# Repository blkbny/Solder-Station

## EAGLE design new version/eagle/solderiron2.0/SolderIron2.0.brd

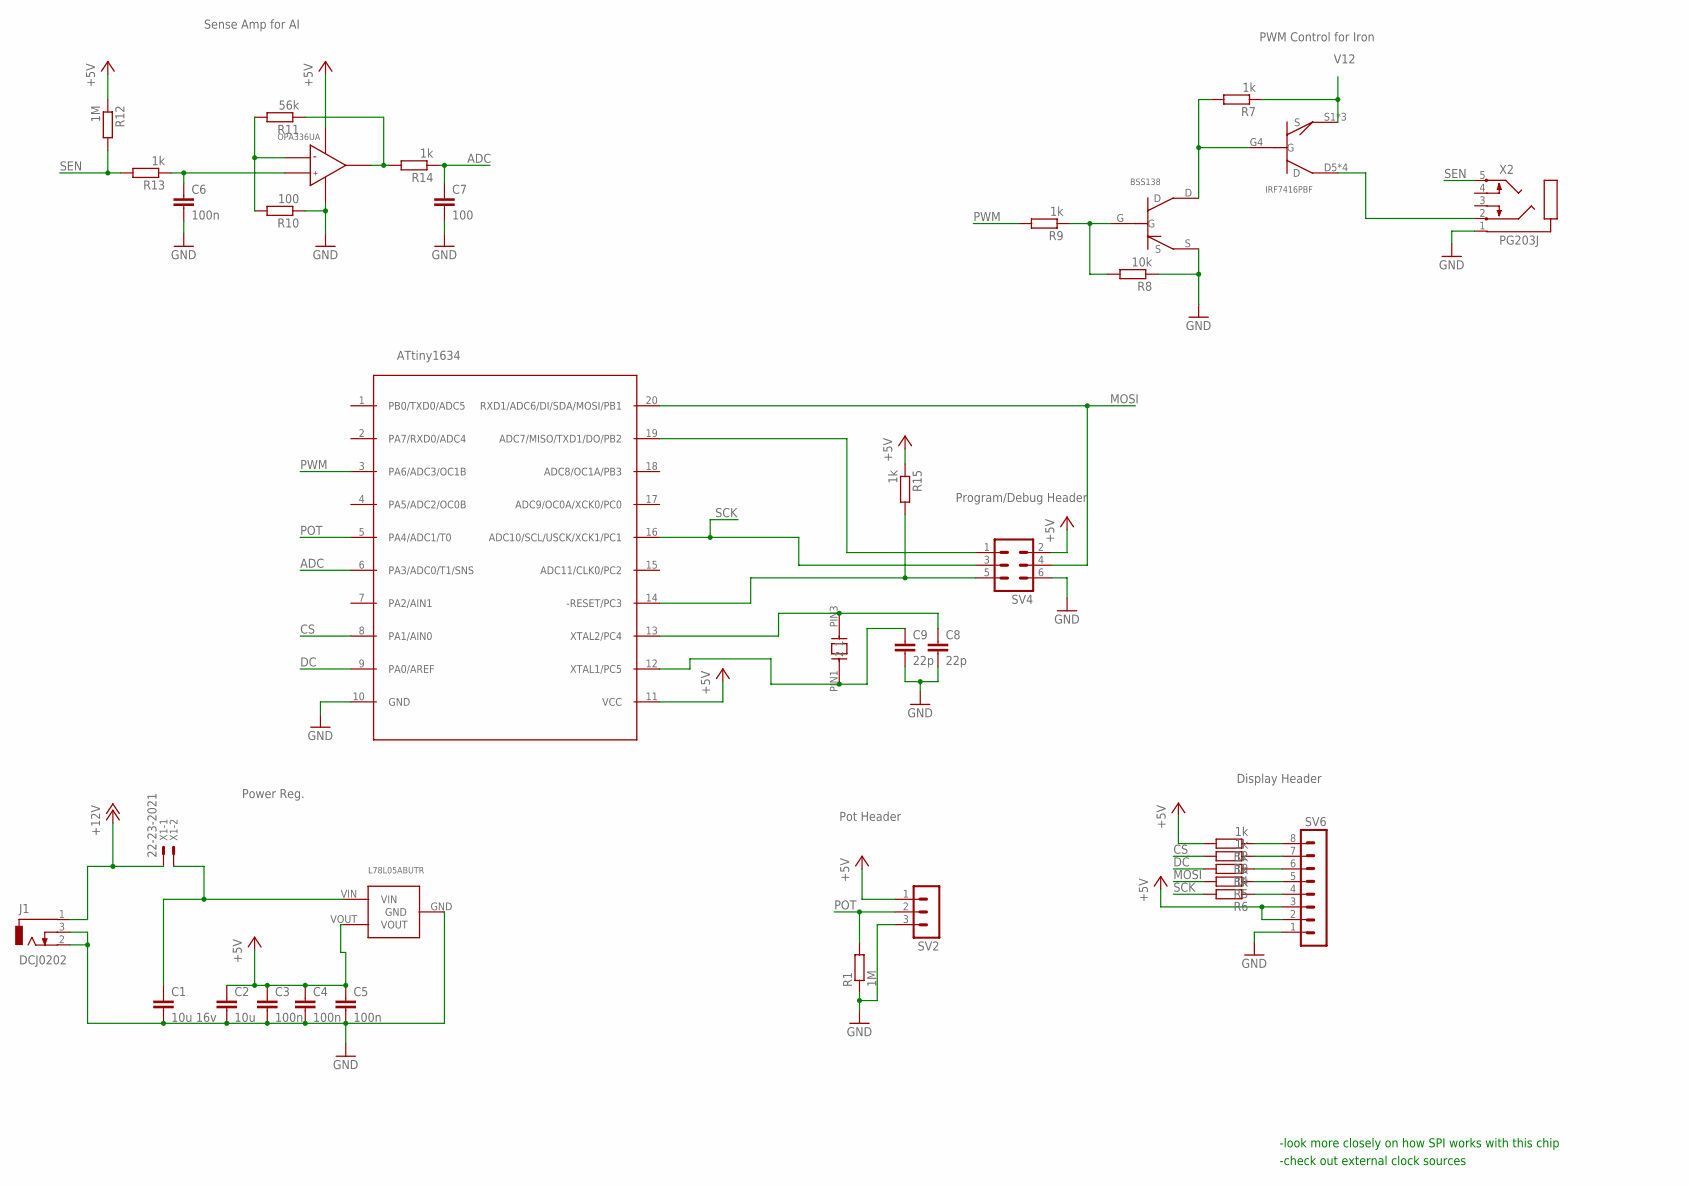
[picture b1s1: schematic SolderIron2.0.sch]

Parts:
C1: 10u 16v; C1206
C2: 10u; C1206
C3, C4, C5, C6: 100n; C1206
C7: 100; C1206
C8, C9: 22p; C1206
J1: DCJ0202; POWERJACK2.1MM
R1, R12: 1M; R0603
R2, R3, R4, R5, R6, R7, R9, R13, R14, R15: 1k; R0603
R8: 10k; R0603
R10: 100; R0603
R11: 56k; R0603
SV2: MA03-1
SV4: MA03-2
SV6: MA08-1
U$1: IRF7416PBF; 8-SOIC
U$2: L78L05ABUTR; SOT89-3
U$3: BSS138; SOT-23
U$4: OPA336UA; 8-SOIC
U$5: ATTINY1634; SOIC20
U$6: CX3225GB12000H0KPSC1; 4-SIZ
X1: 22-23-2021
X2: PG203J

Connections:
+5V: C2.1, C3.1, C4.1, C5.1, R2.2, R12.1, R15.1, SV2.1, SV4.2, SV6.2, SV6.3, U$2.VOUT, U$4.D7 (V+), U$5.11 (VCC)
+12V: J1.1, X1.1
ADC: C7.1, R14.1, U$5.6 (PA3/ADC0/T1/SNS)
CS: R3.2, U$5.8 (PA1/AIN0)
DC: R4.2, U$5.9 (PA0/AREF)
GND: C1.2, C2.2, C3.2, C4.2, C5.2, C6.2, C7.2, C8.2, C9.2, J1.2 (3), J1.3 (2), R1.1, R8.1, R10.1, SV2.3, SV4.6, SV6.1, U$2.GND, U$3.S, U$4.G4 (V-), U$5.10 (GND), X2.1
MOSI: R5.2, SV4.4, U$5.20 (RXD1/ADC6/DI/SDA/MOSI/PB1)
unnamed: C8.1, U$5.13 (XTAL2/PC4), U$6.PIN3 (2)
unnamed: R2.1, SV6.8
unnamed: R3.1, SV6.7
unnamed: R4.1, SV6.6
unnamed: R5.1, SV6.5
unnamed: R6.1, SV6.4
unnamed: U$1.D5 (D), U$1.D6 (D), U$1.D7 (D), U$1.D8 (D), X2.2
unnamed: R7.2, U$1.G4 (G), U$3.D
unnamed: R8.2, R9.1, U$3.G
unnamed: R10.2, R11.2, U$4.S2 (IN-)
unnamed: R11.1, R14.2, U$4.D6 (OUTPUT)
unnamed: C6.1, R13.1, U$4.S3 (IN+)
unnamed: C9.1, U$5.12 (XTAL1/PC5), U$6.PIN1 (1)
unnamed: SV4.1, U$5.19 (ADC7/MISO/TXD1/DO/PB2)
unnamed: R15.2, SV4.5, U$5.14 (-RESET/PC3)
POT: R1.2, SV2.2, U$5.5 (PA4/ADC1/T0)
PWM: R9.2, U$5.3 (PA6/ADC3/OC1B)
SCK: R6.2, SV4.3, U$5.16 (ADC10/SCL/USCK/XCK1/PC1)
SEN: R12.2, R13.2, X2.5
V12: C1.1, R7.1, U$1.S1 (S), U$1.S2 (S), U$1.S3 (S), U$2.VIN, X1.2

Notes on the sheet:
Power Reg.
Pot Header
Display Header
PWM Control for Iron
Sense Amp for AI
Program/Debug Header
-look more closely on how SPI works with this chip
-check out external clock sources

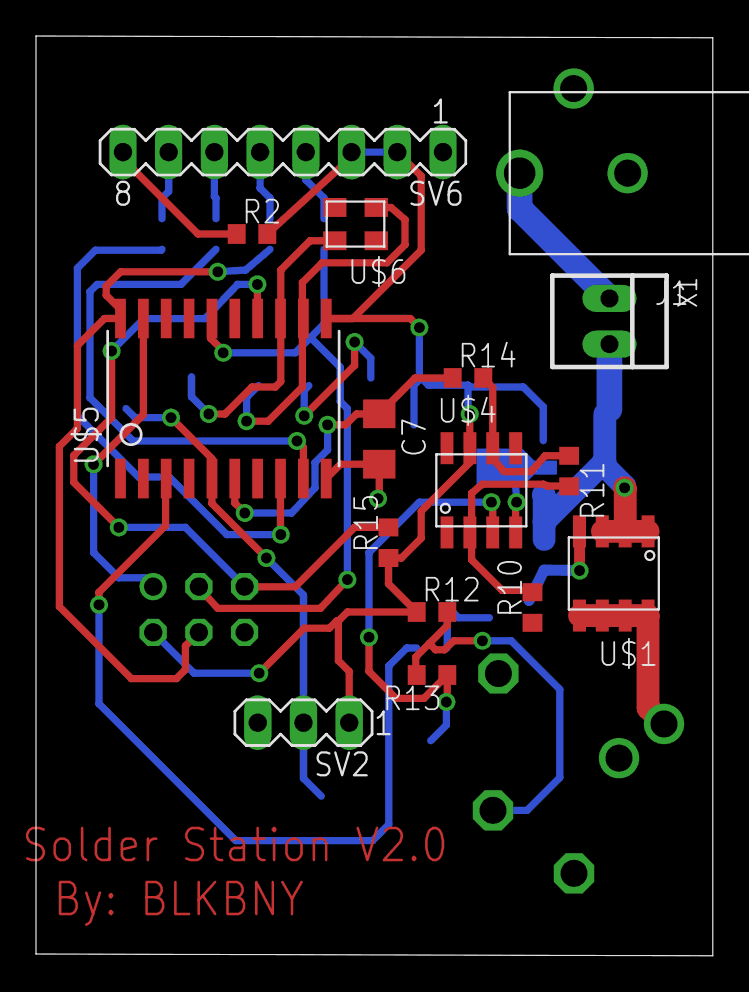
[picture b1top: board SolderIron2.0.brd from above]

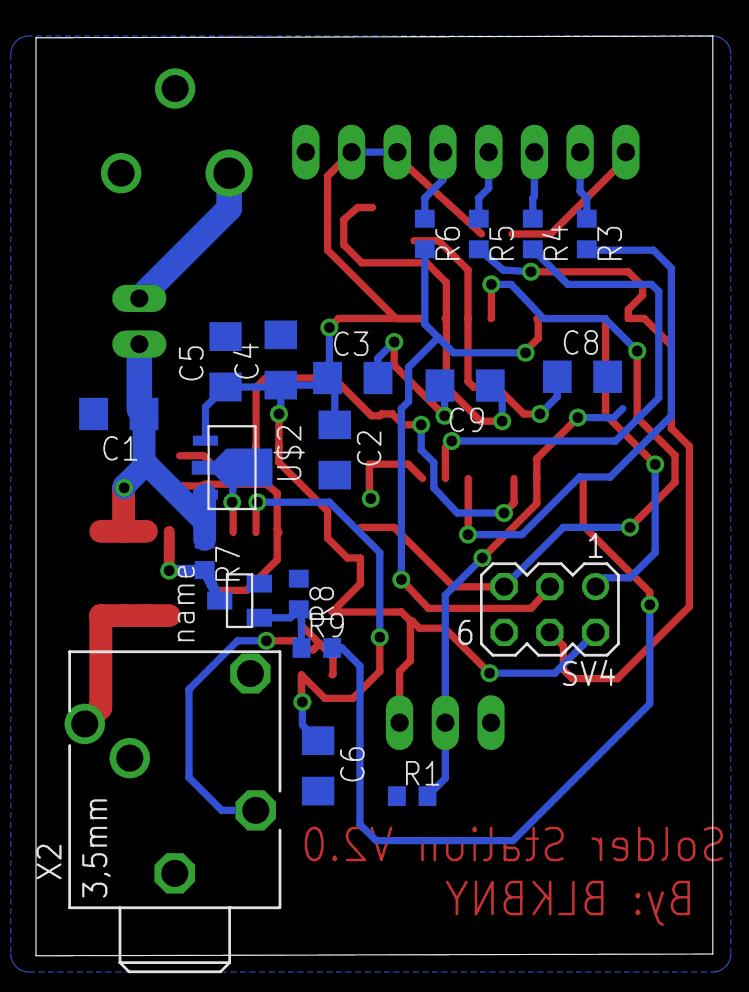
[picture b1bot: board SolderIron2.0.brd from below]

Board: 2 copper layers, 37.6 x 51.1 mm, 36 parts (20 on the bottom side), 27 nets.

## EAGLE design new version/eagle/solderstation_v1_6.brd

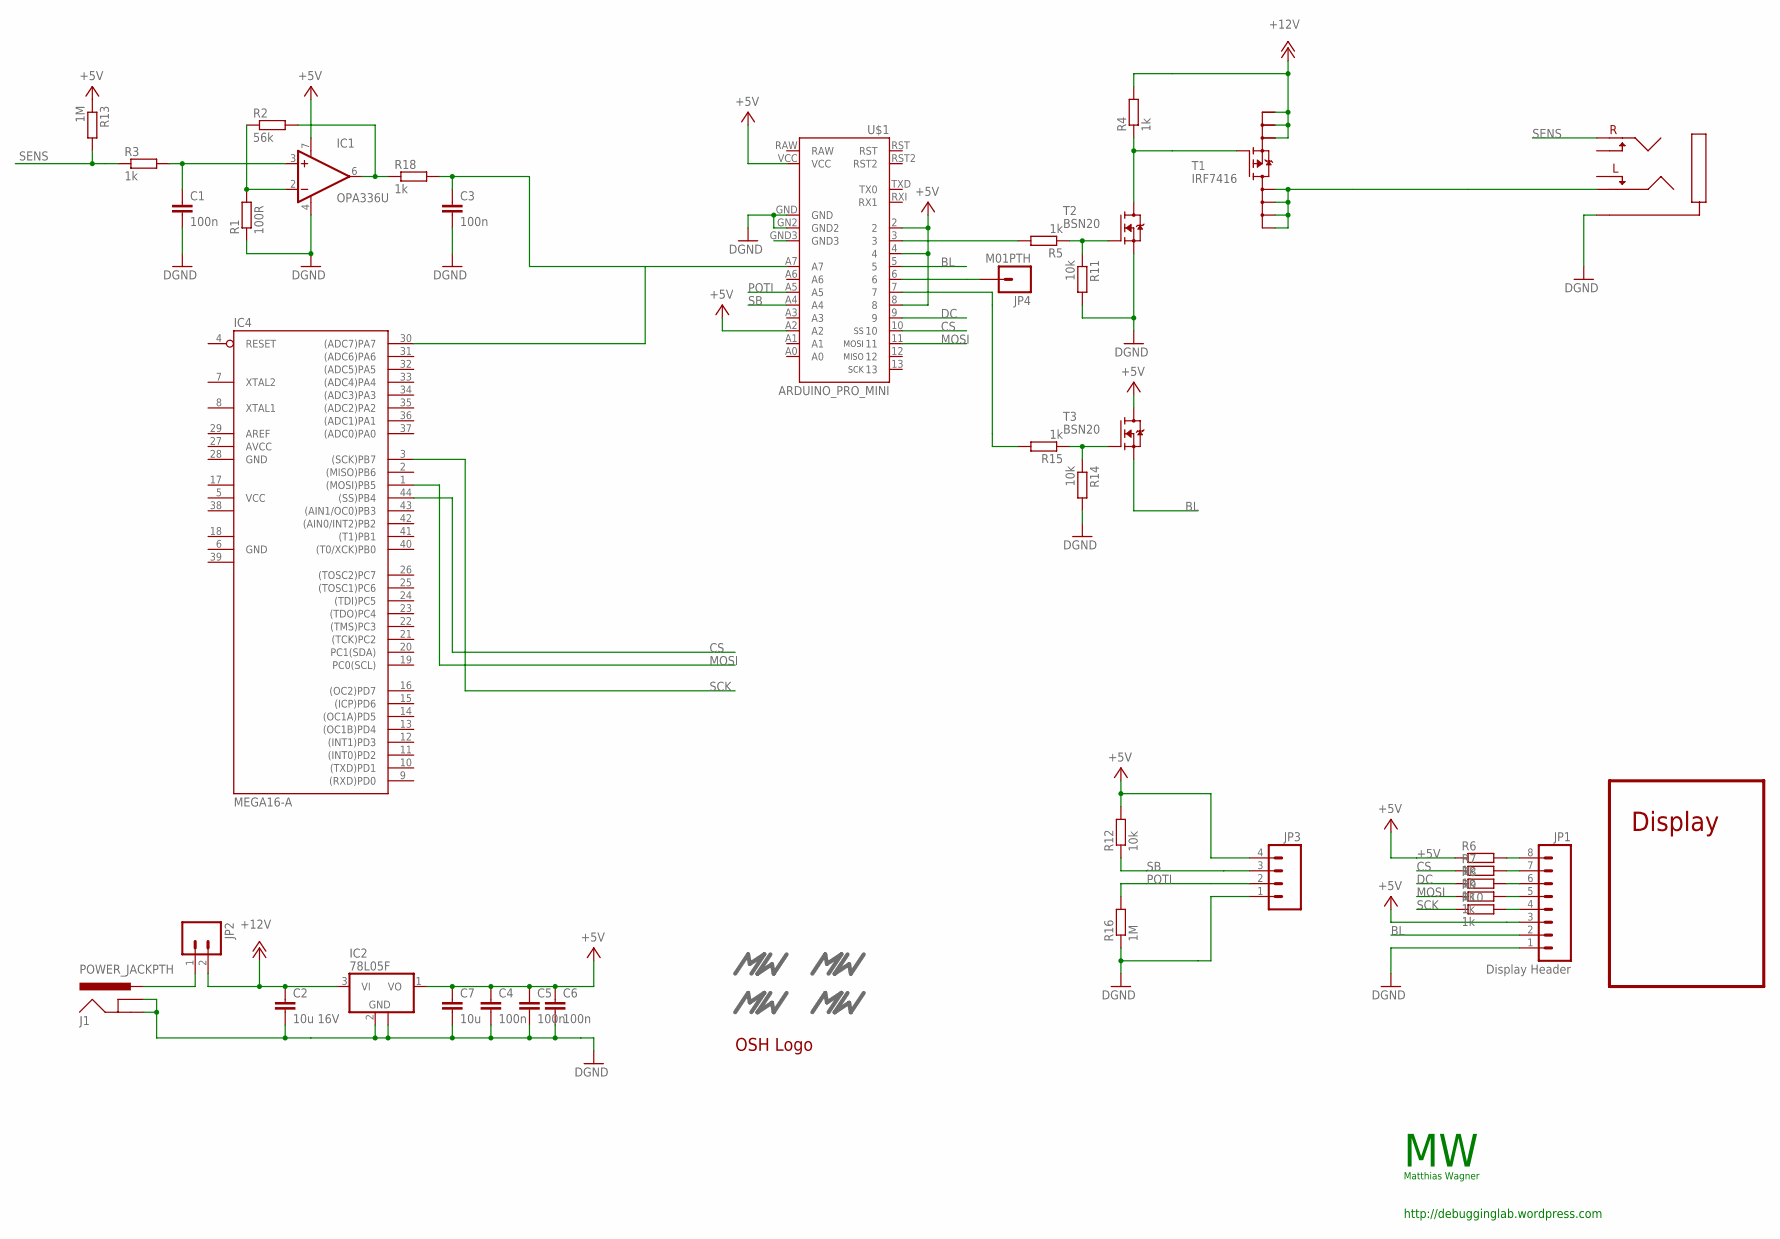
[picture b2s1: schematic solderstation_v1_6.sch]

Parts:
C1, C3, C4, C5, C6: 100n; C0603
C2: 10u 16V; C1206
C7: 10u; C1206
IC1: OPA336U; SO08
IC2: 78L05F; SOT89
IC4: MEGA16-A; TQFP44
J1: POWER_JACKPTH; POWER_JACK_PTH
JP1: Display Header; 1X08_LOCK
JP2: M02LOCK_LONGPADS; 1X02_LOCK_LONGPADS
JP3: M04LOCK; 1X04_LOCK
JP4: M01PTH; 1X01
R1: 100R; R0603
R2: 56k; R0603
R3, R4, R5, R6, R7, R8, R9, R10, R15, R18: 1k; R0603
R11, R12, R14: 10k; R0603
R13, R16: 1M; R0603
T1: IRF7416; SO8
T2, T3: BSN20; SOT23
U$1: ARDUINO_PRO_MINI
U$2: AUDIO_JACK_3,5MMCONRAD; AUDIO_JACK_3,5MM_CONRAD
U$3, U$5: MW_LOGO; MW_11X5MM
U$4, U$9: MW_LOGO_SOLDER; MW_11X5MM_SOLDER
U$8: OSH_LOGOS; OSH_LOGO_S

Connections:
+5V: C4.1, C5.1, C6.1, C7.1, IC1.7 (V+), IC2.1 (VO), JP1.3, JP3.4, R6.1, R12.2, R13.1, T3.3 (D), U$1.2, U$1.4, U$1.8, U$1.A2, U$1.VCC
+12V: C2.1, IC2.3 (VI), JP2.2, R4.2, T1.1 (S0), T1.2 (S1), T1.3 (S2)
BL: JP1.2, T3.2 (S), U$1.5
CS: IC4.44 ((SS)PB4), R7.1, U$1.10
DC: R8.1, U$1.9
DGND: C1.2, C2.2, C3.2, C4.2, C5.2, C6.2, C7.2, IC1.4 (V-), IC2.2 (GND), IC2.2@1 (GND), J1.GND, J1.GNDBREAK, JP1.1, JP3.1, R1.1, R11.2, R14.2, R16.1, T2.2 (S), U$1.GN2 (GND2), U$1.GND, U$2.P_GND
HEATER: T1.5 (D0), T1.6 (D1), T1.7 (D2), T1.8 (D3), U$2.P_LEFT
MOSI: IC4.1 ((MOSI)PB5), R9.1, U$1.11
unnamed: IC1.2 (-IN), R1.2, R2.1
unnamed: IC1.6 (OUT), R2.2, R18.1
unnamed: R5.1, R11.1, T2.1 (G)
unnamed: C1.1, IC1.3 (+IN), R3.2
unnamed: R4.1, T1.4 (G), T2.3 (D)
unnamed: JP1.4, R10.2
unnamed: R5.2, U$1.3
unnamed: JP1.5, R9.2
unnamed: JP1.6, R8.2
unnamed: JP1.7, R7.2
unnamed: JP1.8, R6.2
unnamed: J1.PWR, JP2.1
unnamed: R14.1, R15.1, T3.1 (G)
unnamed: R15.2, U$1.7
unnamed: JP4.1, U$1.6
unnamed: C3.1, IC4.30 ((ADC7)PA7), R18.2, U$1.A7
POTI: JP3.2, R16.2, U$1.A5
SB: JP3.3, R12.1, U$1.A4
SCK: IC4.3 ((SCK)PB7), R10.1, U$1.13
SENS: R3.1, R13.2, U$2.P_RIGHT

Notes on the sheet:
Display
http://debugginglab.wordpress.com
Matthias Wagner

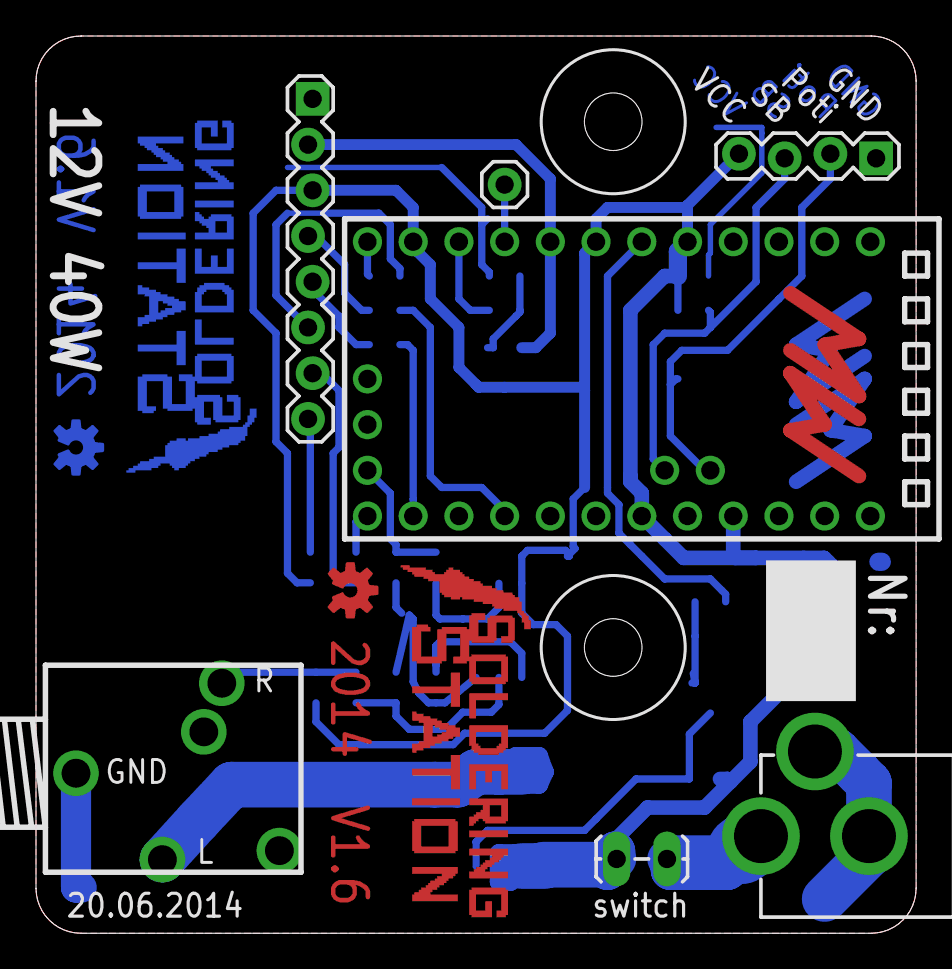
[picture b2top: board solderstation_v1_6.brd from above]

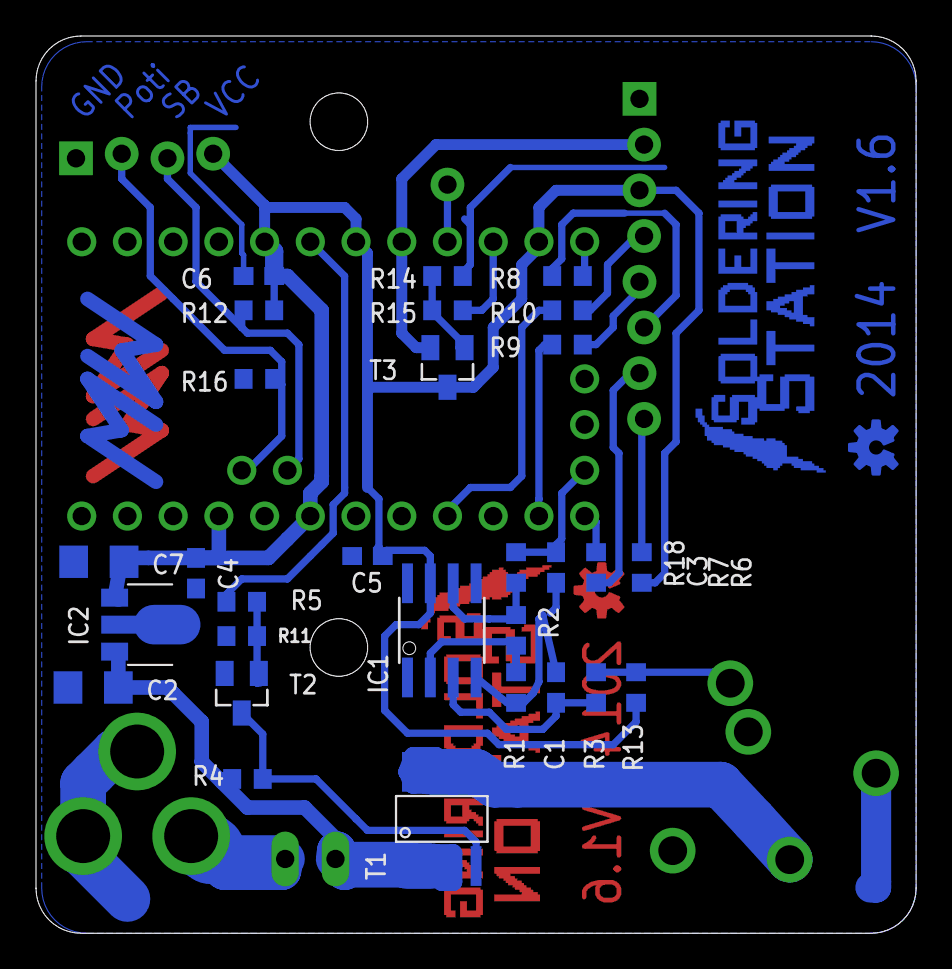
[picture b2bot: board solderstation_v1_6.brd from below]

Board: 2 copper layers, 48.9 x 49.8 mm, 44 parts (33 on the bottom side), 28 nets.

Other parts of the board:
U$6, U$7: SOLDER_STATION19,5MM_BOT; SOLDER_STATION_19,5MM_BOT
U$10: OSH_LOGOS; OSH_LOGO_S

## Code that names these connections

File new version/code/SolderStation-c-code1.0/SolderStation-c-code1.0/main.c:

/*
 * SolderStation-c-code1.0.c
 *
 * Created: 12/15/2015 2:21:16 PM
 * Author : Dperreault
 */ 

#include <avr/io.h>


int main(void)
{
    /* Replace with your application code */
    while (1) 
    {
    }
}

void init_hardwr(void)
{
	//set both PA0 and PA1 as outputs for DC and CS to control LCD
	DDRA = (0<<DDRA0 | 0<<DDRA1) //init pins PA0-PA1 as outputs
	
	//set PC1, PB1, and PB2 as SPI data com
	//init SPI
	
	//set PA3 as ADC0 for reading analog temp from iron
	//init ADC0
	
	//set PA4 as ADC1 for reading analog from potent. to set temp
	//init ADC1
	
	//set PA6 as PWM for Iron temp control
	//init PWM 
	
}

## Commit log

2015-12-15 adding open source base project for modification
2015-12-15 added basic proto code
2015-12-17 basic code update: added better descriptions for init routine and init CS and DC for LCD screen
2015-12-18 added another solder project for reference
2015-12-21 new commit
2015-12-21 added eagle lib for components
2015-12-21 added powersupply circuit
2015-12-22 created eagle schematics
2015-12-22 adding eagle lib
2015-12-23 finished v2 schematic
2015-12-23 first board setup
2015-12-30 getting code to work
2016-01-03 got code to work
2016-01-04 created new PCB layout
2016-01-05 finished PCB part layout
2016-01-11 routed new board
2016-01-11 added title to PCB
2016-01-11 added Gerber files for V2.0
2016-01-12 adjusted LCD logo coloring

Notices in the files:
parts and their libraries:
SparkFun: Licensing: CC v3.0 Share-Alike You are welcome to use this library for commercial purposes.
